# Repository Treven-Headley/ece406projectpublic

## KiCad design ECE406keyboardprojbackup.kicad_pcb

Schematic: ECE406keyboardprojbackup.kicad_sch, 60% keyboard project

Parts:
C17, C18: 100n; C_0805_2012Metric; Manufacturer Part Number CC0805KRX7R9BB104
C19, C20, C21, C22, C23, C24, C25, C26, C27, C28, C29, C30, C31, C32, C33, C34, C35, C36, C37, C38, C39, C40, C41, C42, C43, C44, C45, C46, C47, C48, C49, C50, C51, C52, C53, C54, C55, C56, C57, C58, C59, C60, C61, C62, C63, C64, C65, C66, C67, C68, C69, C70, C71, C72, C73, C74, C75, C76, C77, C78: 100n; C_0402_1005Metric; Manufacturer Part Number CC0402KRX7R8BB104
CB1: 1uF; C_0402_1005Metric
CB2: 10n; C_0402_1005Metric
CB3, CB5, CB8: 100n; C_0402_1005Metric
CB4, CB6: 4.7uF; C_0402_1005Metric
CB7: 100nF; C_0402_1005Metric
CRST1: 10u; C_0805_2012Metric_Pad1.15x1.40mm_HandSolder
CRST2: 4.7n; C_0805_2012Metric_Pad1.15x1.40mm_HandSolder
CSH1: 4.7nF; C_0805_2012Metric
CSI1: 10u; C_0805_2012Metric_Pad1.15x1.40mm_HandSolder
CSO1: 1u; C_0805_2012Metric_Pad1.15x1.40mm_HandSolder
CUSB1: 100n; C_0402_1005Metric
D1, D2, D3, D4, D5, D6, D7, D8, D9, D10, D11, D12, D13, D14, D15, D16, D17, D18, D19, D20, D21, D22, D23, D24, D25, D26, D27, D28, D29, D30, D31, D32, D33, D34, D35, D36, D37, D38, D39, D40, D41, D42, D43, D44, D45, D46, D47, D48, D49, D50, D51, D52, D53, D54, D55, D56, D57, D58, D59, D60: 1N4148; D_SOD-123
D61, D62, D63, D64, D65, D66, D67, D68, D69, D70, D71, D72, D73, D74, D75, D76, D77, D78, D79, D80, D81, D82, D83, D84, D85, D86, D87, D88, D89, D90, D91, D92, D93, D94, D95, D96, D97, D98, D99, D100, D101, D102, D103, D104, D105, D106, D107, D108, D109, D110, D111, D112, D113, D114, D115, D116, D117, D118, D119, D120: SK6812MINI-E; SK6812MINI_3535_6028_3.2x2.8mm_Round; Manufacturer Part Number SK812MINI-E
DF1: RB060M-60TR; D_SOD-123
DRST1: 1N4148; D_SOD-123
DS1: 1N4148; D_SOD-123
F1: Polyfuse; Fuse_1812_4532
H2: Mounting Hole; MoutingHole_Oval_7mm_5.0x2.5mm
H3: Oval Mounting Hole; MoutingHole_Oval_BackOnly_7mm_5.0x2.5mm
H5: Oval Mounting Hole; MoutingHole_Oval_7mm_5.0x2.5mm
J1: TYPE-C-31-M12_13; TYPE-C-31-M-12
J2: Conn_ARM_JTAG_SWD_10
QRST1: DTC123J; SOT-23
R1, R2, R3, R4, R5, R6, R7, R8, R9, R10, R11, R13, R14, R15, R16, R17, R18, R19, R20, R21, R22, R23, R24, R25, R26, R27, R28, R29, R30, R31, R32, R33, R34, R35, R36, R37, R38, R39, R40, R41, R42, R43, R44, R45, R46, R47, R48, R49, R50, R51, R52, R53, R54, R55, R56, R57, R58, R59, R60, R61: 5.1R; R_0402_1005Metric; Manufacturer Part Number WR04X5R1JTL
R12: 10k; R_0805_2012Metric; Manufacturer Part Number RC0805FR-0710KL
RCC1, RCC2: 5.1k; R_0402_1005Metric
RRST1: 100k; R_SMD_1026
RSH1: 1M; R_SMD_1026
SW1: ESC; MX100H
SW2: 1; MX100H
SW3: 2; MX100H
SW4: 3; MX100H
SW5: 4; MX100H
SW6: 5; MX100H
SW7: 6; MX100H
SW8: 7; MX100H
SW9: 8; MX100H
SW10: 9; MX100H
SW11: 0; MX100H
SW12: -_; MX100H
SW13: =+; MX100H
SW14: BKSP_200; MX200HR
SW15: TAB_150; MX150H
SW16: Q; MX100H
SW17: W; MX100H
SW18: E; MX100H
SW19: R; MX100H
SW20: T; MX100H
SW21: Y; MX100H
SW22: U; MX100H
SW23: I; MX100H
SW24, SW38: L; MX100H
SW25: O; MX100H
SW26: P; MX100H
SW27: [{; MX100H
SW28: ]}; MX150H
SW29: CAPS_175; MX175H
SW30: A; MX100H
SW31: S; MX100H
SW32: D; MX100H
SW33: F; MX100H
SW34: G; MX100H
SW35: H; MX100H
SW36: J; MX100H
SW37: K; MX100H
SW39: :;; MX100H
SW40: "; MX100H
SW41: ENTER_225; MX225HR
SW42: LSHIFT_225; MX225HR
SW43: Z; MX100H
SW44: X; MX100H
SW45: C; MX100H
SW46: V; MX100H
SW47: B; MX100H
SW48: N; MX100H
SW49: M; MX100H
SW50: <,; MX100H
SW51: .>; MX100H
SW52: ?/; MX100H
SW53: RSHIFT_275; MX275HR
SW54, SW56, SW58, SW60: MXSwitch; MX150H
SW55, SW59: MXSwitch; MX100H
SW57: MXSwitch; MX700H
SWRST1: SW_Push; smdPushBtn
U1: STM32F072-LQFP48; LQFP-48_7x7mm_P0.5mm
U2: USBLC6-2SC6; SOT-23-6
U3: MCP1700-3302E_SOT23; SOT-23
U4: TXS0101DBVR; SOT95P280X145-6N

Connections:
3V3: C17.2, CB1.2, CB2.2, CB3.2, CB4.2, CB5.2, CB6.2, CB7.1, CB8.2, CSO1.2, DS1.2 (A), J2.1 (VTref), R12.1, SWRST1.1, U1.1 (VBAT), U1.9 (VDDA), U1.24 (VDD), U1.36 (VDDIO2), U1.48 (VDD), U3.2 (VO), U4.1 (VCCA)
5V: C18.1, CSI1.2, DF1.1 (K), DS1.1 (K), F1.1, R1.2, R2.2, R3.2, R4.2, R5.2, R6.2, R7.2, R8.2, R9.2, R10.2, R11.2, R13.2, R14.2, R15.2, R16.2, R17.2, R18.2, R19.2, R20.2, R21.2, R22.2, R23.2, R24.2, R25.2, R26.2, R27.2, R28.2, R29.2, R30.2, R31.2, R32.2, R33.2, R34.2, R35.2, R36.2, R37.2, R38.2, R39.2, R40.2, R41.2, R42.2, R43.2, R44.2, R45.2, R46.2, R47.2, R48.2, R49.2, R50.2, R51.2, R52.2, R53.2, R54.2, R55.2, R56.2, R57.2, R58.2, R59.2, R60.2, R61.2, U3.3 (VI), U4.6 (VCCB)
/SHIELD: CSH1.2, J1.S (SHIELD), RSH1.1
BOOT0: CRST1.2, DRST1.1 (K), RRST1.1, U1.44 (BOOT0)
Col1: SW1.1 (Col), SW15.1 (Col), SW29.1 (Col), SW42.1 (Col), SW54.1 (Col), U1.25 (PB12)
Col2: SW2.1 (Col), SW16.1 (Col), SW30.1 (Col), SW43.1 (Col), SW55.1 (Col), U1.11 (PA1/ADC_IN1)
Col3: SW3.1 (Col), SW17.1 (Col), SW31.1 (Col), SW44.1 (Col), SW56.1 (Col), U1.10 (PA0/ADC_IN0)
Col4: SW4.1 (Col), SW18.1 (Col), SW32.1 (Col), SW45.1 (Col), U1.6 (PF1/OSC_OUT)
Col5: SW5.1 (Col), SW19.1 (Col), SW33.1 (Col), SW46.1 (Col), U1.5 (PF0/OSC_IN)
Col6: SW6.1 (Col), SW20.1 (Col), SW34.1 (Col), SW47.1 (Col), U1.4 (PC15/OSC32_OUT)
Col7: SW7.1 (Col), SW21.1 (Col), SW35.1 (Col), SW48.1 (Col), SW57.1 (Col), U1.3 (PC14/OSC32_IN)
Col8: SW8.1 (Col), SW22.1 (Col), SW36.1 (Col), SW49.1 (Col), U1.2 (PC13)
Col9: SW9.1 (Col), SW23.1 (Col), SW37.1 (Col), SW50.1 (Col), U1.46 (SPI2_NSS/I2S2_WS/I2C1_SDA/TIM17_CH1/PB9)
Col10: SW10.1 (Col), SW24.1 (Col), SW38.1 (Col), SW51.1 (Col), SW58.1 (Col), U1.45 (I2C1_SCL/TIM16_CH1/PB8)
Col11: SW11.1 (Col), SW25.1 (Col), SW39.1 (Col), SW52.1 (Col), SW59.1 (Col), U1.43 (2C1_SDA/PB7)
Col12: SW12.1 (Col), SW26.1 (Col), SW40.1 (Col), SW53.1 (Col), SW60.1 (Col), U1.42 (I2C1_SCL/PB6)
Col13: SW13.1 (Col), SW14.1 (Col), SW27.1 (Col), SW28.1 (Col), SW41.1 (Col), U1.41 (SPI1_MOSI/I2S1_SD/TIM3_CH2/PB5)
D+: U1.33 (USB_DP/PA12), U2.3 (IO2)
D-: U1.32 (USB_DM/TIM1_CH4/PA11), U2.1 (IO1)
DBus+: J1.A7 (D-), J1.B7 (D-), U2.4 (IO2)
DBus-: J1.A6 (D+), J1.B6 (D+), U2.6 (IO1)
GND: C17.1, C18.2, C19.2, C20.2, C21.2, C22.2, C23.2, C24.2, C25.2, C26.2, C27.2, C28.2, C29.2, C30.2, C31.2, C32.2, C33.2, C34.2, C35.2, C36.2, C37.2, C38.2, C39.2, C40.2, C41.2, C42.2, C43.2, C44.2, C45.2, C46.2, C47.2, C48.2, C49.2, C50.2, C51.2, C52.2, C53.2, C54.2, C55.2, C56.2, C57.2, C58.2, C59.2, C60.2, C61.2, C62.2, C63.2, C64.2, C65.2, C66.2, C67.2, C68.2, C69.2, C70.2, C71.2, C72.2, C73.2, C74.2, C75.2, C76.2, C77.2, C78.2, CB1.1, CB2.1, CB3.1, CB4.1, CB5.1, CB6.1, CB7.2, CB8.1, CRST1.1, CRST2.2, CSH1.1, CSI1.1, CSO1.1, CUSB1.1, D61.3 (VSS), D62.3 (VSS), D63.3 (VSS), D64.3 (VSS), D65.3 (VSS), D66.3 (VSS), D67.3 (VSS), D68.3 (VSS), D69.3 (VSS), D70.3 (VSS), D71.3 (VSS), D72.3 (VSS), D73.3 (VSS), D74.3 (VSS), D75.3 (VSS), D76.3 (VSS), D77.3 (VSS), D78.3 (VSS), D79.3 (VSS), D80.3 (VSS), D81.3 (VSS), D82.3 (VSS), D83.3 (VSS), D84.3 (VSS), D85.3 (VSS), D86.3 (VSS), D87.3 (VSS), D88.3 (VSS), D89.3 (VSS), D90.3 (VSS), D91.3 (VSS), D92.3 (VSS), D93.3 (VSS), D94.3 (VSS), D95.3 (VSS), D96.3 (VSS), D97.3 (VSS), D98.3 (VSS), D99.3 (VSS), D100.3 (VSS), D101.3 (VSS), D102.3 (VSS), D103.3 (VSS), D104.3 (VSS), D105.3 (VSS), D106.3 (VSS), D107.3 (VSS), D108.3 (VSS), D109.3 (VSS), D110.3 (VSS), D111.3 (VSS), D112.3 (VSS), D113.3 (VSS), D114.3 (VSS), D115.3 (VSS), D116.3 (VSS), D117.3 (VSS), D118.3 (VSS), D119.3 (VSS), D120.3 (VSS), DF1.2 (A), J1.A1 (GND), J1.B1 (GND), J2.3 (GND), J2.5 (GND), J2.9 (GNDDetect), QRST1.2 (E), RCC1.1, RCC2.1, RRST1.2, RSH1.2, U1.8 (VSSA), U1.23 (VSS), U1.35 (VSS), U1.47 (VSS), U2.2 (GND), U3.1 (GND), U4.2 (GND)
NRST: CRST2.1, J2.10 (~RESET), QRST1.3 (C), U1.7 (NRST)
unnamed: C19.1, D61.1 (VDD), R1.1
unnamed: C20.1, D62.1 (VDD), R6.1
unnamed: C21.1, D63.1 (VDD), R10.1
unnamed: C22.1, D64.1 (VDD), R16.1
unnamed: C23.1, D65.1 (VDD), R20.1
unnamed: C24.1, D66.1 (VDD), R24.1
unnamed: C25.1, D67.1 (VDD), R29.1
unnamed: C26.1, D68.1 (VDD), R33.1
unnamed: C27.1, D69.1 (VDD), R37.1
unnamed: C28.1, D70.1 (VDD), R42.1
unnamed: C29.1, D71.1 (VDD), R47.1
unnamed: C30.1, D72.1 (VDD), R52.1
unnamed: C31.1, D73.1 (VDD), R56.1
unnamed: C32.1, D74.1 (VDD), R58.1
unnamed: C33.1, D75.1 (VDD), R59.1
unnamed: C34.1, D76.1 (VDD), R57.1
unnamed: C35.1, D77.1 (VDD), R53.1
unnamed: C36.1, D78.1 (VDD), R48.1
unnamed: C37.1, D79.1 (VDD), R43.1
unnamed: C38.1, D80.1 (VDD), R38.1
unnamed: C39.1, D81.1 (VDD), R34.1
unnamed: C40.1, D82.1 (VDD), R30.1
unnamed: C41.1, D91.1 (VDD), R25.1
unnamed: C42.1, D83.1 (VDD), R21.1
unnamed: C43.1, D84.1 (VDD), R17.1
unnamed: C44.1, D85.1 (VDD), R11.1
unnamed: C45.1, D86.1 (VDD), R7.1
unnamed: C46.1, D87.1 (VDD), R2.1
unnamed: C47.1, D88.1 (VDD), R3.1
unnamed: C48.1, D89.1 (VDD), R8.1
unnamed: C49.1, D90.1 (VDD), R13.1
unnamed: C50.1, D92.1 (VDD), R18.1
unnamed: C51.1, D93.1 (VDD), R22.1
unnamed: C52.1, D94.1 (VDD), R26.1
unnamed: C53.1, D95.1 (VDD), R31.1
unnamed: C54.1, D96.1 (VDD), R35.1
unnamed: C55.1, D97.1 (VDD), R39.1
unnamed: C56.1, D98.1 (VDD), R44.1
unnamed: C57.1, D99.1 (VDD), R49.1
unnamed: C58.1, D100.1 (VDD), R54.1
unnamed: C59.1, D101.1 (VDD), R60.1
unnamed: C60.1, D102.1 (VDD), R61.1
unnamed: C61.1, D103.1 (VDD), R55.1
unnamed: C62.1, D104.1 (VDD), R50.1
unnamed: C63.1, D105.1 (VDD), R45.1
unnamed: C64.1, D106.1 (VDD), R40.1
unnamed: C65.1, D107.1 (VDD), R36.1
unnamed: C66.1, D108.1 (VDD), R32.1
unnamed: C67.1, D109.1 (VDD), R27.1
unnamed: C68.1, D110.1 (VDD), R23.1
unnamed: C69.1, D111.1 (VDD), R19.1
unnamed: C70.1, D112.1 (VDD), R14.1
unnamed: C71.1, D113.1 (VDD), R4.1
unnamed: C72.1, D114.1 (VDD), R5.1
unnamed: C73.1, D115.1 (VDD), R9.1
unnamed: C74.1, D116.1 (VDD), R15.1
unnamed: C75.1, D117.1 (VDD), R28.1
unnamed: C76.1, D118.1 (VDD), R41.1
unnamed: C77.1, D119.1 (VDD), R46.1
unnamed: C78.1, D120.1 (VDD), R51.1
unnamed: D1.2 (A), SW1.2 (Row)
unnamed: D2.2 (A), SW2.2 (Row)
unnamed: D3.2 (A), SW3.2 (Row)
unnamed: D4.2 (A), SW4.2 (Row)
unnamed: D5.2 (A), SW5.2 (Row)
unnamed: D6.2 (A), SW6.2 (Row)
unnamed: D7.2 (A), SW7.2 (Row)
unnamed: D8.2 (A), SW8.2 (Row)
unnamed: D9.2 (A), SW9.2 (Row)
unnamed: D10.2 (A), SW10.2 (Row)
unnamed: D11.2 (A), SW11.2 (Row)
unnamed: D12.2 (A), SW12.2 (Row)
unnamed: D13.2 (A), SW13.2 (Row)
unnamed: D14.2 (A), SW14.2 (Row)
unnamed: D15.2 (A), SW15.2 (Row)
unnamed: D16.2 (A), SW16.2 (Row)
unnamed: D17.2 (A), SW17.2 (Row)
unnamed: D18.2 (A), SW18.2 (Row)
unnamed: D19.2 (A), SW19.2 (Row)
unnamed: D20.2 (A), SW20.2 (Row)
unnamed: D21.2 (A), SW21.2 (Row)
unnamed: D22.2 (A), SW22.2 (Row)
unnamed: D23.2 (A), SW23.2 (Row)
unnamed: D24.2 (A), SW24.2 (Row)
unnamed: D25.2 (A), SW25.2 (Row)
unnamed: D26.2 (A), SW26.2 (Row)
unnamed: D27.2 (A), SW27.2 (Row)
unnamed: D28.2 (A), SW28.2 (Row)
unnamed: D29.2 (A), SW29.2 (Row)
unnamed: D30.2 (A), SW30.2 (Row)
unnamed: D31.2 (A), SW31.2 (Row)
unnamed: D32.2 (A), SW32.2 (Row)
unnamed: D33.2 (A), SW33.2 (Row)
unnamed: D34.2 (A), SW34.2 (Row)
unnamed: D35.2 (A), SW35.2 (Row)
unnamed: D36.2 (A), SW36.2 (Row)
unnamed: D37.2 (A), SW37.2 (Row)
unnamed: D38.2 (A), SW38.2 (Row)
unnamed: D39.2 (A), SW39.2 (Row)
unnamed: D40.2 (A), SW40.2 (Row)
unnamed: D41.2 (A), SW41.2 (Row)
unnamed: D42.2 (A), SW42.2 (Row)
unnamed: D43.2 (A), SW43.2 (Row)
unnamed: D44.2 (A), SW44.2 (Row)
unnamed: D45.2 (A), SW45.2 (Row)
unnamed: D46.2 (A), SW46.2 (Row)
unnamed: D47.2 (A), SW47.2 (Row)
unnamed: D48.2 (A), SW48.2 (Row)
unnamed: D49.2 (A), SW49.2 (Row)
unnamed: D50.2 (A), SW50.2 (Row)
unnamed: D51.2 (A), SW51.2 (Row)
unnamed: D52.2 (A), SW52.2 (Row)
unnamed: D53.2 (A), SW53.2 (Row)
unnamed: D54.2 (A), SW54.2 (Row)
unnamed: D55.2 (A), SW55.2 (Row)
unnamed: D56.2 (A), SW56.2 (Row)
unnamed: D57.2 (A), SW57.2 (Row)
unnamed: D58.2 (A), SW58.2 (Row)
unnamed: D59.2 (A), SW59.2 (Row)
unnamed: D60.2 (A), SW60.2 (Row)
unnamed: D61.2 (DOUT), D62.4 (DIN)
unnamed: D62.2 (DOUT), D63.4 (DIN)
unnamed: D63.2 (DOUT), D64.4 (DIN)
unnamed: D64.2 (DOUT), D65.4 (DIN)
unnamed: D65.2 (DOUT), D66.4 (DIN)
unnamed: D66.2 (DOUT), D67.4 (DIN)
unnamed: D67.2 (DOUT), D68.4 (DIN)
unnamed: D68.2 (DOUT), D69.4 (DIN)
unnamed: D69.2 (DOUT), D70.4 (DIN)
unnamed: D70.2 (DOUT), D71.4 (DIN)
unnamed: D71.2 (DOUT), D72.4 (DIN)
unnamed: D72.2 (DOUT), D73.4 (DIN)
unnamed: D73.2 (DOUT), D74.4 (DIN)
unnamed: D74.2 (DOUT), D75.4 (DIN)
unnamed: D75.2 (DOUT), D76.4 (DIN)
unnamed: D76.2 (DOUT), D77.4 (DIN)
unnamed: D77.2 (DOUT), D78.4 (DIN)
unnamed: D78.2 (DOUT), D79.4 (DIN)
unnamed: D79.2 (DOUT), D80.4 (DIN)
unnamed: D80.2 (DOUT), D81.4 (DIN)
unnamed: D81.2 (DOUT), D82.4 (DIN)
unnamed: D82.2 (DOUT), D91.4 (DIN)
unnamed: D83.2 (DOUT), D84.4 (DIN)
unnamed: D83.4 (DIN), D91.2 (DOUT)
unnamed: D84.2 (DOUT), D85.4 (DIN)
unnamed: D85.2 (DOUT), D86.4 (DIN)
unnamed: D86.2 (DOUT), D87.4 (DIN)
unnamed: D87.2 (DOUT), D88.4 (DIN)
unnamed: D88.2 (DOUT), D89.4 (DIN)
unnamed: D89.2 (DOUT), D90.4 (DIN)
unnamed: D90.2 (DOUT), D92.4 (DIN)
unnamed: D92.2 (DOUT), D93.4 (DIN)
unnamed: D93.2 (DOUT), D94.4 (DIN)
unnamed: D94.2 (DOUT), D95.4 (DIN)
unnamed: D95.2 (DOUT), D96.4 (DIN)
unnamed: D96.2 (DOUT), D97.4 (DIN)
unnamed: D97.2 (DOUT), D98.4 (DIN)
unnamed: D98.2 (DOUT), D99.4 (DIN)
unnamed: D100.2 (DOUT), D101.4 (DIN)
unnamed: D99.2 (DOUT), D100.4 (DIN)
unnamed: D101.2 (DOUT), D102.4 (DIN)
unnamed: D102.2 (DOUT), D103.4 (DIN)
unnamed: D103.2 (DOUT), D104.4 (DIN)
unnamed: D104.2 (DOUT), D105.4 (DIN)
unnamed: D105.2 (DOUT), D106.4 (DIN)
unnamed: D106.2 (DOUT), D107.4 (DIN)
unnamed: D107.2 (DOUT), D108.4 (DIN)
unnamed: D108.2 (DOUT), D109.4 (DIN)
unnamed: D109.2 (DOUT), D110.4 (DIN)
unnamed: D110.2 (DOUT), D111.4 (DIN)
unnamed: D111.2 (DOUT), D112.4 (DIN)
unnamed: D112.2 (DOUT), D113.4 (DIN)
unnamed: D113.2 (DOUT), D114.4 (DIN)
unnamed: D114.2 (DOUT), D115.4 (DIN)
unnamed: D115.2 (DOUT), D116.4 (DIN)
unnamed: D116.2 (DOUT), D117.4 (DIN)
unnamed: D117.2 (DOUT), D118.4 (DIN)
unnamed: D118.2 (DOUT), D119.4 (DIN)
unnamed: D119.2 (DOUT), D120.4 (DIN)
unnamed: DRST1.2 (A), QRST1.1 (B), SWRST1.2
unnamed: J1.A5 (CC1), RCC1.2
unnamed: J1.B5 (CC2), RCC2.2
unnamed: R12.2, U4.5 (OE)
RGB_3V3: U1.28 (SPI2_MOSI/I2S2_SD/PB15), U4.3 (A)
RGB_5V: D61.4 (DIN), U4.4 (B)
RGB_OUT: D120.2 (DOUT)
Row1: D1.1 (K), D2.1 (K), D3.1 (K), D4.1 (K), D5.1 (K), D6.1 (K), D7.1 (K), D8.1 (K), D9.1 (K), D10.1 (K), D11.1 (K), D12.1 (K), D13.1 (K), U1.40 (SPI1_MISO/I2S1_MCK/TIM3_CH1/PB4)
Row2: D15.1 (K), D16.1 (K), D17.1 (K), D18.1 (K), D19.1 (K), D20.1 (K), D21.1 (K), D22.1 (K), D23.1 (K), D24.1 (K), D25.1 (K), D26.1 (K), D27.1 (K), U1.39 (SPI1_SCK/I2S1_CK/TIM2_CH2/PB3)
Row3: D29.1 (K), D30.1 (K), D31.1 (K), D32.1 (K), D33.1 (K), D34.1 (K), D35.1 (K), D36.1 (K), D37.1 (K), D38.1 (K), D39.1 (K), D40.1 (K), D41.1 (K), U1.12 (PA2/ADC_IN2)
Row4: D14.1 (K), D42.1 (K), D43.1 (K), D44.1 (K), D45.1 (K), D46.1 (K), D47.1 (K), D48.1 (K), D49.1 (K), D50.1 (K), D51.1 (K), D52.1 (K), D53.1 (K), U1.13 (PA3/TIM15_CH2/ADC_IN3)
Row5: D28.1 (K), D54.1 (K), D55.1 (K), D56.1 (K), D57.1 (K), D58.1 (K), D59.1 (K), D60.1 (K), U1.14 (PA4/TIM14_CH1/ADC_IN4)
SWCLK: J2.4 (SWDCLK/TCK), U1.37 (SWCLK/PA14)
SWDIO: J2.2 (SWDIO/TMS), U1.34 (SWDIO/PA13)
VBUS: CUSB1.2, F1.2, J1.A4 (VBUS), J1.B4 (VBUS), U2.5 (VBUS)

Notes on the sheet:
MINUS
RIGHT GUI
Power supply circuit
Reset circuit
TAB
LEFT CONTROL
RIGHT BRACKET
SPACE
CAPS LOCK
FN2 MENU
SLASH
QUOTE
COLON
ENTER
USB Connector and ESD
Serial Wire Debug (SWD)
COMMA
MCU
BACKSPACE
Shield
LEFT ALT
SW8 was skipped to make firmware easier for the ISO tilde
BACKSLASH
MIGHT need to move Col8 to another pin
DOT
LEFT BRACKET
PLUS
SW8 was skipped to make firmware easier for the ISO backslash
LEFT SHIFT
esc
LEFT GUI
RIGHT ALT
SW5 was skipped to make firmware easier for the split right shift
RIGHT SHIFT

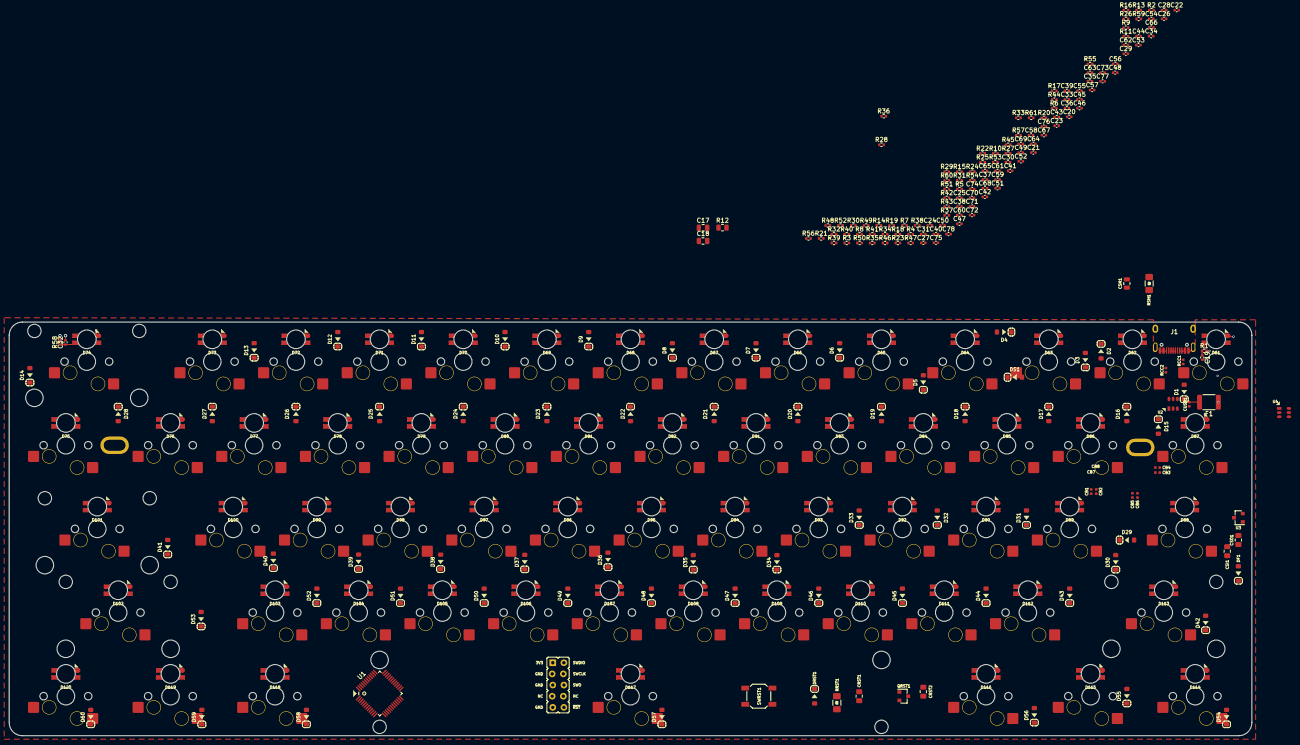
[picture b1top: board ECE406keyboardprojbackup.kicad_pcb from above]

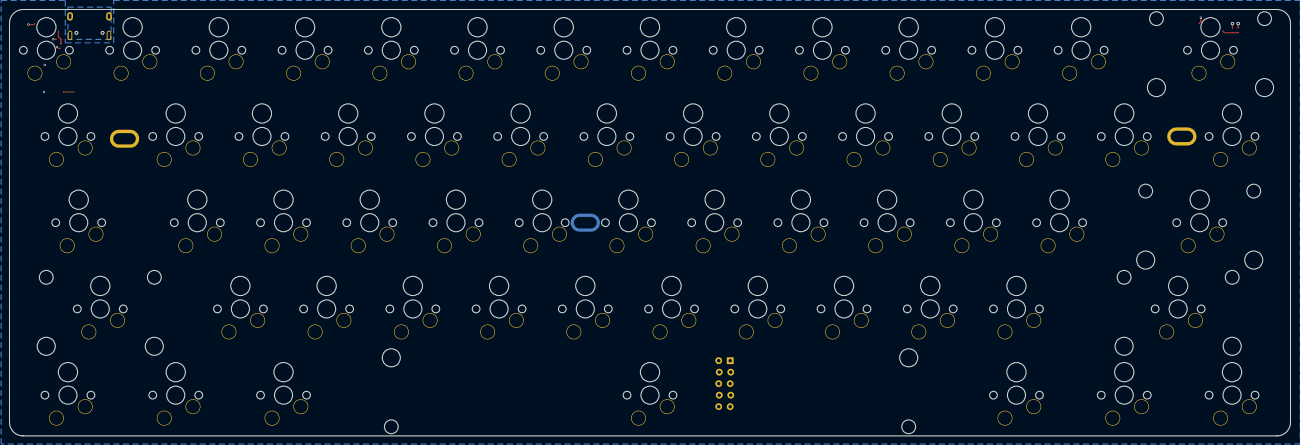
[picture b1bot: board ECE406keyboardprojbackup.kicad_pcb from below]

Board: 4 copper layers, 283.0 x 94.2 mm, 336 parts (3 on the bottom side), 216 nets.
